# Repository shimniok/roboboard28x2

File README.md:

# roboboard28x2
Robot controller board for PICAXE-28X2.

Built for 5th grade robotics club that I'm leading. It's a low cost "baseboard" for the
PICAXE with built-in USB connector and FTDI chip.

By using an onboard FTDI we save versus the retail cost of FTDI breakout boards which are
also easy to lose.

Breaks out each pin with a corresponding VCC and GND for convenient hookup of sensors and
controllers.

The board has a footprint for a Pololu S10V4F5 step-up/step-down switching regulator
daughterboard (or anything with an equivalent pinout) to provide a steady 5V from 4AA 
batteries for sake of predictability.

Also expects to use a separate motor control board (using the Pololu DRV8835 breakout in
this case but any low voltage motor controller will work).

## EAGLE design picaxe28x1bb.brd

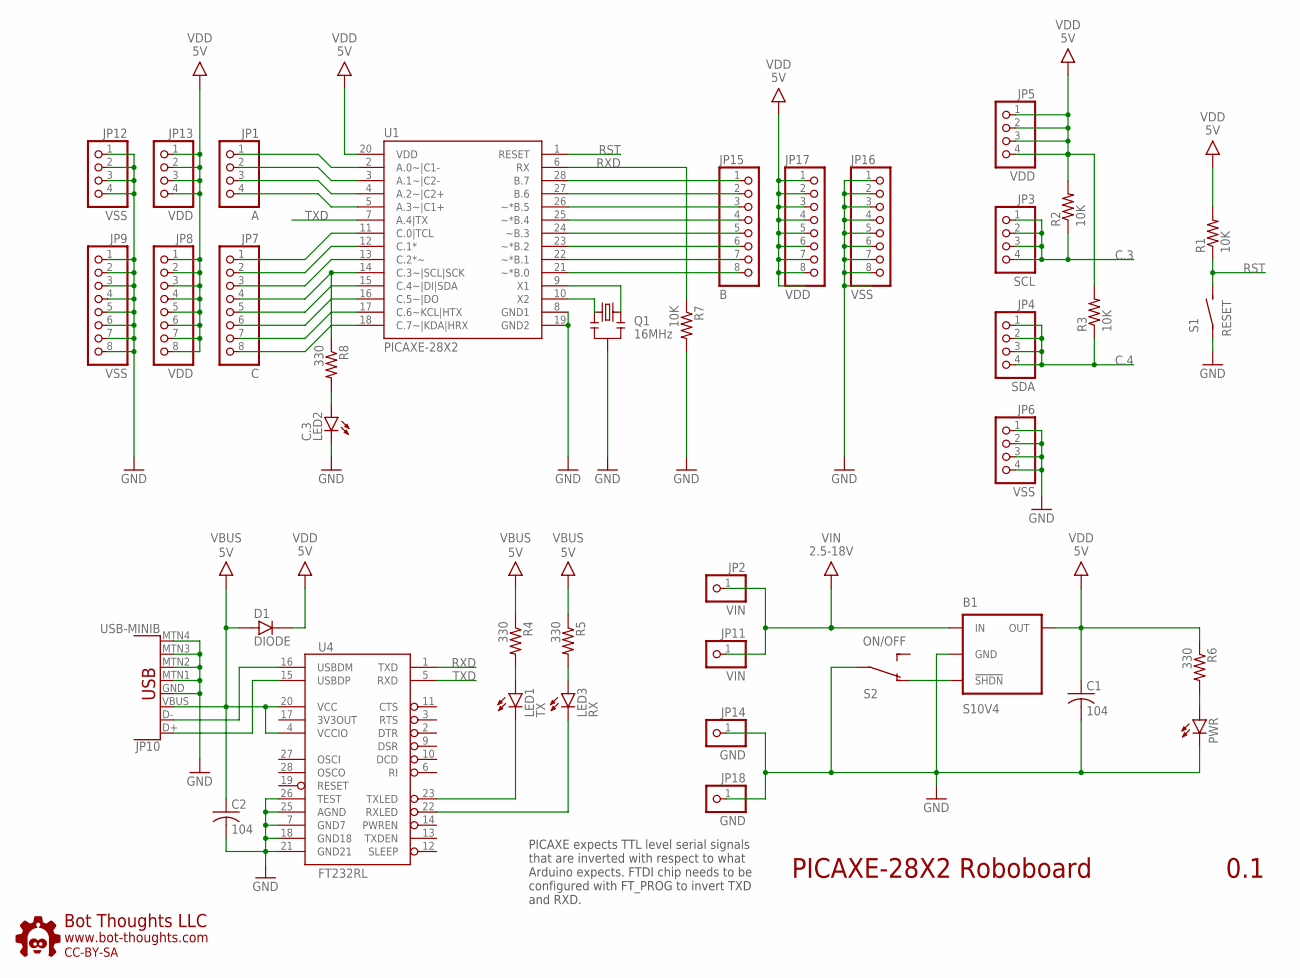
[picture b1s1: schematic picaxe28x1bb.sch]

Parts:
B1: S10V4; POLOLU-S10V4
C1, C2: 104; C0603
D1: DIODE; SOD123FL
JP1: A; 1X04-S
JP2, JP11: VIN; 1X01-S
JP3: SCL; 1X04-S
JP4: SDA; 1X04-S
JP5, JP13: VDD; 1X04-S
JP6, JP12: VSS; 1X04-S
JP7: C; 1X08-S
JP8, JP17: VDD; 1X08-S
JP9, JP16: VSS; 1X08-S
JP10: USB-MINIB
JP14, JP18: GND; 1X01-S
JP15: B; 1X08-S
LED1: TX; CHIPLED_0805
LED2: C.3; CHIPLED_1206
LED3: RX; CHIPLED_0805
PWR: LEDCHIPLED_1206; CHIPLED_1206
Q1: 16MHz; CSTCE_V_C
R1, R2, R3, R7: 10K; R0603
R4, R5, R6, R8: 330; R0603
S1: RESET; 3X4X2TACT
S2: ON/OFF; OS102011MA1Q
U1: PICAXE-28X2; DIL28-3
U4: FT232RL; SSOP28DB
U$10: BTLOGO-LOGO-MD; BTLOGOM

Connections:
A.0: JP1.1, U1.2 (A.0~|C1-)
A.1: JP1.2, U1.3 (A.1~|C2-)
A.2: JP1.3, U1.4 (A.2~|C2+)
A.3: JP1.4, U1.5 (A.3~|C1+)
B.0: JP15.8, U1.21 (~*B.0)
B.1: JP15.7, U1.22 (~*B.1)
B.2: JP15.6, U1.23 (~*B.2)
B.3: JP15.5, U1.24 (~B.3)
B.4: JP15.4, U1.25 (~*B.4)
B.5: JP15.3, U1.26 (~*B.5)
B.6: JP15.2, U1.27 (B.6)
B.7: JP15.1, U1.28 (B.7)
C.0: JP7.1, U1.11 (C.0|TCL)
C.1: JP7.2, U1.12 (C.1*)
C.2: JP7.3, U1.13 (C.2*~)
C.3: JP3.1, JP3.2, JP3.3, JP3.4, JP7.4, R2.1, R8.1, U1.14 (C.3~|SCL|SCK)
C.4: JP4.1, JP4.2, JP4.3, JP4.4, JP7.5, R3.1, U1.15 (C.4~|DI|SDA)
C.5: JP7.6, U1.16 (C.5~|DO)
C.6: JP7.7, U1.17 (C.6~KCL|HTX)
C.7: JP7.8, U1.18 (C.7~|KDA|HRX)
EN: B1.!SHDN, S2.P$1 (O1)
GND: B1.GND, C1.2, C2.2, JP6.1, JP6.2, JP6.3, JP6.4, JP9.1, JP9.2, JP9.3, JP9.4, JP9.5, JP9.6, JP9.7, JP9.8, JP10.GND, JP10.MTN1 (SHIELD1), JP10.MTN2 (SHIELD2), JP10.MTN3 (SHIELD3), JP10.MTN4 (SHIELD4), JP12.1, JP12.2, JP12.3, JP12.4, JP14.1, JP16.1, JP16.2, JP16.3, JP16.4, JP16.5, JP16.6, JP16.7, JP16.8, JP18.1, LED2.C, PWR.C, Q1.GND, R7.2, S1.P$1, S2.P$2, U1.8 (GND1), U1.19 (GND2), U4.7 (GND7), U4.18 (GND18), U4.21 (GND21), U4.25 (AGND), U4.26 (TEST)
unnamed: LED2.A, R8.2
unnamed: PWR.A, R6.2
unnamed: LED1.C, U4.23 (TXLED)
unnamed: LED1.A, R4.2
unnamed: LED3.A, R5.2
unnamed: JP10.D-, U4.16 (USBDM)
unnamed: JP10.D+, U4.15 (USBDP)
unnamed: LED3.C, U4.22 (RXLED)
unnamed: Q1.X2, U1.10 (X2)
unnamed: Q1.X1, U1.9 (X1)
RST: R1.1, S1.P$2 (S), U1.1 (RESET)
RXD: R7.1, U1.6 (RX), U4.1 (TXD)
TXD: U1.7 (A.4|TX), U4.5 (RXD)
VBUS: C2.1, D1.A, JP10.VBUS, R4.1, R5.1, U4.4 (VCCIO), U4.20 (VCC)
VDD: B1.VOUT (OUT), C1.1, D1.C, JP5.1, JP5.2, JP5.3, JP5.4, JP8.1, JP8.2, JP8.3, JP8.4, JP8.5, JP8.6, JP8.7, JP8.8, JP13.1, JP13.2, JP13.3, JP13.4, JP17.1, JP17.2, JP17.3, JP17.4, JP17.5, JP17.6, JP17.7, JP17.8, R1.2, R2.2, R3.2, R6.1, U1.20 (VDD)
VIN: B1.VIN (IN), JP2.1, JP11.1

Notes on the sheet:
PICAXE expects TTL level serial signals that are inverted with respect to what Arduino expects. FTDI chip needs to be configured with FT_PROG to invert TXD and RXD.
PICAXE-28X2 Roboboard
0.1

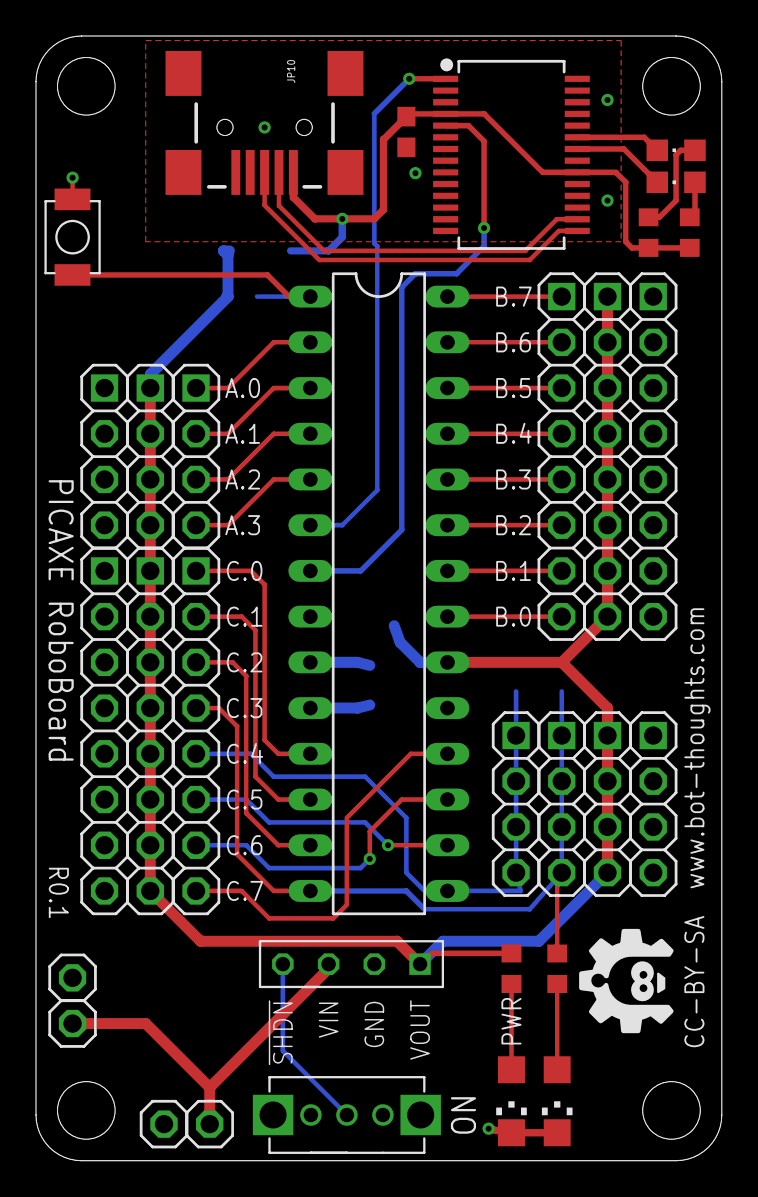
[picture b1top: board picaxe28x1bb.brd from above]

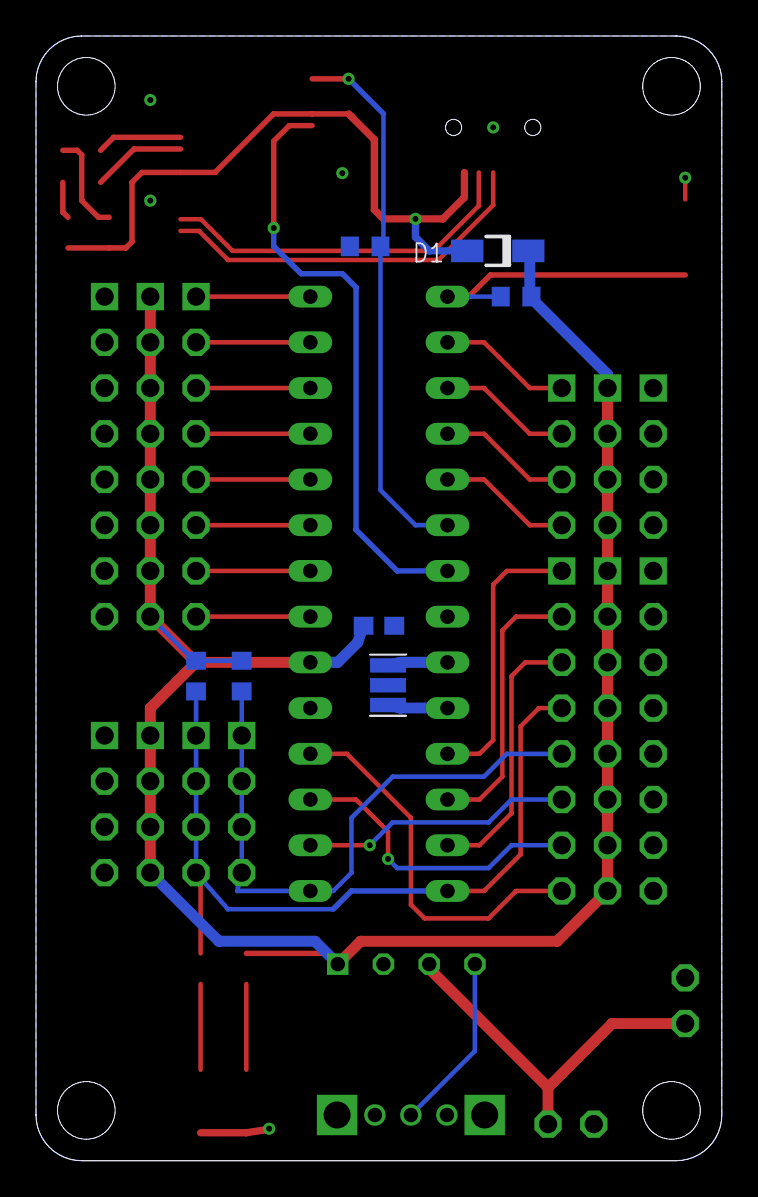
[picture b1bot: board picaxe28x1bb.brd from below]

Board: 2 copper layers, 38.1 x 62.5 mm, 40 parts (7 on the bottom side), 38 nets.

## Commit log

2016-11-27 initial version
2016-11-28 updated layout, leds, inverted serial, etc.
2016-11-29 addition of FTDI, usb mini b, layout updates

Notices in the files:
picaxe28x1bb.brd:
CC-BY-SA
parts and their libraries:
SparkFun-DigitalIC: Licensing: Creative Commons ShareAlike 4.0 International - https://creativecommons.org/licenses/by-sa/4.0
